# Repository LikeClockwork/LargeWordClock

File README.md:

# Like Clockwork Large Word Clock Design Files and Software

This repository holds the PCB/laser etch design files and Arduino code for my version of the word clock.

These PCBs and the laser cut glass faces are currently available via my store at: http://www.likeclockworkdesign.com/collections/kits/products/the-standard-makers-kit

The PCB measures 399x399mm and the glass faceplace measures 17"x17".

The PCBs are Arduino compatible and it runs the “Arduino on a breadboard” bootloader. The microcontroller is a Atmega328p (TQFP package) running at 8MHz that drives two 16x8 LED (256 LEDs) matrixes via two HT16K33’s. Time keeping is accomplished using a DS321 real time clock.  There is a linear power regulator on board to step down 9-12V input voltage to 5V. 

All unused Arduino pins are broken out to a pin header. Happy hacking!

The posted PCBs have been fabricated, assembled, and confirmed as working with the posted code.

*Upcoming Changes:*

The boards shipped ~~for the Kickstarter~~ going forward will have the following enhancements:
+ Addition of a footprint so that you can plug in standard Arduino shields. Done!

+ The ability to replace all ICs with prebuilt modules (Arduino Nano vs. Atmega328p, Adafruit matrix drivers vs. HT16K33s) for those who don’t want to drag solder tiny leads. Done!

+ Addition of a prototyping area to make use of all that extra real-estate. Done!

+ Addition of an Open Source Hardware logo. Done!

*Thanks to:*

+ The Kickstarter Backers
+ CERN for building KiCad and making it free.
+ Adafruit for their great libraries and making awesome breakout boards.

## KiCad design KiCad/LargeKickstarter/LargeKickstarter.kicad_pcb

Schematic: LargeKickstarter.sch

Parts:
0-0, 0-1, 0-2, 0-3, 0-4, 0-5, 0-6, 0-7, 0-8, 0-9, 0-10, 0-11, 0-12, 0-13, 0-14, 0-15, 0-16, 0-17, 0-18, 0-19, 0-20, 0-21, 0-22, 0-23, 0-24, 0-25, 0-26, 0-27, 0-28, 0-29, 0-30, 0-31, 1-0, 1-1, 1-2, 1-3, 1-4, 1-5, 1-6, 1-7, 1-8, 1-9, 1-10, 1-11, 1-12, 1-13, 1-14, 1-15, 1-16, 1-17, 1-18, 1-19, 1-20, 1-21, 1-22, 1-23, 1-24, 1-25, 1-26, 1-27, 1-28, 1-29, 1-30, 1-31, 2-0, 2-1, 2-2, 2-3, 2-4, 2-5, 2-6, 2-7, 2-8, 2-9, 2-10, 2-11, 2-12, 2-13, 2-14, 2-15, 2-16, 2-17, 2-18, 2-19, 2-20, 2-21, 2-22, 2-23, 2-24, 2-25, 2-26, 2-27, 2-28, 2-29, 2-30, 2-31, 3-0, 3-1, 3-2, 3-3, 3-4, 3-5, 3-6, 3-7, 3-8, 3-9, 3-10, 3-11, 3-12, 3-13, 3-14, 3-15, 3-16, 3-17, 3-18, 3-19, 3-20, 3-21, 3-22, 3-23, 3-24, 3-25, 3-26, 3-27, 3-28, 3-29, 3-30, 3-31, 4-0, 4-1, 4-2, 4-3, 4-4, 4-5, 4-6, 4-7, 4-8, 4-9, 4-10, 4-11, 4-12, 4-13, 4-14, 4-15, 4-16, 4-17, 4-18, 4-19, 4-20, 4-21, 4-22, 4-23, 4-24, 4-25, 4-26, 4-27, 4-28, 4-29, 4-30, 4-31, 5-0, 5-1, 5-2, 5-3, 5-4, 5-5, 5-6, 5-7, 5-8, 5-9, 5-10, 5-11, 5-12, 5-13, 5-14, 5-15, 5-16, 5-17, 5-18, 5-19, 5-20, 5-21, 5-22, 5-23, 5-24, 5-25, 5-26, 5-27, 5-28, 5-29, 5-30, 5-31, 6-0, 6-1, 6-2, 6-3, 6-4, 6-5, 6-6, 6-7, 6-8, 6-9, 6-10, 6-11, 6-12, 6-13, 6-14, 6-15, 6-16, 6-17, 6-18, 6-19, 6-20, 6-21, 6-22, 6-23, 6-24, 6-25, 6-26, 6-27, 6-28, 6-29, 6-30, 6-31, 7-0, 7-1, 7-2, 7-3, 7-4, 7-5, 7-6, 7-7, 7-8, 7-9, 7-10, 7-11, 7-12, 7-13, 7-14, 7-15, 7-16, 7-17, 7-18, 7-19, 7-20, 7-21, 7-22, 7-23, 7-24, 7-25, 7-26, 7-27, 7-28, 7-29, 7-30, 7-31, 8-0, 8-1, 8-2, 8-3, 8-4, 8-5, 8-6, 8-7, 8-8, 8-9, 8-10, 8-11, 8-12, 8-13, 8-14, 8-15, 8-16, 8-17, 8-18, 8-19, 8-20, 8-21, 8-22, 8-23, 8-24, 8-25, 8-26, 8-27, 8-28, 8-29, 8-30, 8-31, 9-0, 9-1, 9-2, 9-3, 9-4, 9-5, 9-6, 9-7, 9-8, 9-9, 9-10, 9-11, 9-12, 9-13, 9-14, 9-15, 9-16, 9-17, 9-18, 9-19, 9-20, 9-21, 9-22, 9-23, 9-24, 9-25, 9-26, 9-27, 9-28, 9-29, 9-30, 9-31, 10-0, 10-1, 10-2, 10-3, 10-4, 10-5, 10-6, 10-7, 10-8, 10-9, 10-10, 10-11, 10-12, 10-13, 10-14, 10-15, 10-16, 10-17, 10-18, 10-19, 10-20, 10-21, 10-22, 10-23, 10-24, 10-25, 10-26, 10-27, 10-28, 10-29, 10-30, 10-31, 11-0, 11-1, 11-2, 11-3, 11-4, 11-5, 11-6, 11-7, 11-8, 11-9, 11-10, 11-11, 11-12, 11-13, 11-14, 11-15, 11-16, 11-17, 11-18, 11-19, 11-20, 11-21, 11-22, 11-23, 11-24, 11-25, 11-26, 11-27, 11-28, 11-29, 11-30, 11-31, 12-0, 12-1, 12-2, 12-3, 12-4, 12-5, 12-6, 12-7, 12-8, 12-9, 12-10, 12-11, 12-12, 12-13, 12-14, 12-15, 12-16, 12-17, 12-18, 12-19, 12-20, 12-21, 12-22, 12-23, 12-24, 12-25, 12-26, 12-27, 12-28, 12-29, 12-30, 12-31, 13-0, 13-1, 13-2, 13-3, 13-4, 13-5, 13-6, 13-7, 13-8, 13-9, 13-10, 13-11, 13-12, 13-13, 13-14, 13-15, 13-16, 13-17, 13-18, 13-19, 13-20, 13-21, 13-22, 13-23, 13-24, 13-25, 13-26, 13-27, 13-28, 13-29, 13-30, 13-31, 14-0, 14-1, 14-2, 14-3, 14-4, 14-5, 14-6, 14-7, 14-8, 14-9, 14-10, 14-11, 14-12, 14-13, 14-14, 14-15, 14-16, 14-17, 14-18, 14-19, 14-20, 14-21, 14-22, 14-23, 14-24, 14-25, 14-26, 14-27, 14-28, 14-29, 14-30, 14-31, 15-0, 15-1, 15-2, 15-3, 15-4, 15-5, 15-6, 15-7, 15-8, 15-9, 15-10, 15-11, 15-12, 15-13, 15-14, 15-15, 15-16, 15-17, 15-18, 15-19, 15-20, 15-21, 15-22, 15-23, 15-24, 15-25, 15-26, 15-27, 15-28, 15-29, 15-30, 15-31: LED; SMD_LED_PLCC_2
BT1: BATTERY; BATTCOM_20MM_PTH
C1, C4, C5, C6, C7, C8: 0.1uF; C_0603_HandSoldering
C2: 10uF; Elko_vert_11.2x7.5mm_RM2.5_CopperClear
C3: 1uF; Elko_vert_11.2x7.5mm_RM2.5_CopperClear
D1: DIODE; Diode-SMA_Handsoldering
D2, D3, D4, D5: DIODE; SOD-323
JP1, JP2, JP3, JP4, JP5, JP6, JP7, JP8, JP9, JP10, JP11, JP12: JUMPER; solder_jumper
P1: CONN_01X03; Diode_TO-220_Dual_CommonCathode_Horizontal_LargePads
P2: CONN_01X02; Pin_Header_Straight_1x02
P4: CONN_02X03; Pin_Header_Straight_2x03
R1, R2, R4, R5, R7: 10K; R_0603_HandSoldering
R3, R6, R8, R9, R10, R11, R12, R13, R14, R15, R16, R17: 47K; R_0603_HandSoldering
SW1: HOUR; TACTILE-PTH-SIDEEZ
SW2: MIN; TACTILE-PTH-SIDEEZ
SW4: SOFT; TACTILE-PTH-SIDEEZ
U1, U4, U10, U12: HT16K33; SO28W
U2: DS3231; SOIC-16_7.5x10.3mm_Pitch1.27mm
U3: ATMEGA328-TQFP; TQFP32-08
U5, U6, U9, U11: HT16K33_BOUT; HT16K33_Breakout
U7: Arduino_Nano
U8: UNO_FOOTPRINT; shield_footprint

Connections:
2: U3.32 (2), U7.5 (2), U8.30 (2)
3: U3.1 (3), U7.6 (3), U8.29 (3)
3.3V: U7.29 (3.3V), U8.4 (3.3V)
4: U3.2 (4), U7.7 (4), U8.28 (4)
5: R1.1, SW1.2, U3.9 (5), U7.8 (5), U8.27 (5); also elsewhere on the board
6: R2.1, SW2.2, U3.10 (6), U7.9 (6), U8.26 (6); also elsewhere on the board
7: R5.1, SW4.2, U3.11 (7), U7.10 (7), U8.25 (7); also elsewhere on the board
8: U3.12 (8), U7.11 (8), U8.24 (8)
9: U3.13 (9), U7.12 (9), U8.23 (9)
10: U3.14 (10), U7.13 (10/SS), U8.22 (10)
A0: U3.23 (A0), U7.27 (A0), U8.9 (A0)
A1: U3.24 (A1), U7.26 (A1), U8.10 (A1)
A2: U3.25 (A2), U7.25 (A2), U8.11 (A2)
A3: U3.26 (A3), U7.24 (A3), U8.12 (A3)
A6: U3.19 (A6), U7.21 (A6)
A7: U3.22 (A7), U7.20 (A7)
AREF: U3.20 (AREF), U7.28 (AREF), U8.17 (AREF)
COM-0-0: 0-0.2 (K), 1-0.2 (K), 2-0.2 (K), 3-0.2 (K), 4-0.2 (K), 5-0.2 (K), 6-0.2 (K), 7-0.2 (K), 8-0.2 (K), 9-0.2 (K), 10-0.2 (K), 11-0.2 (K), 12-0.2 (K), 13-0.2 (K), 14-0.2 (K), 15-0.2 (K), D3.2 (A), U1.2 (COM0/AD), U5.2 (COM0/A0)
COM-0-1: 0-1.2 (K), 1-1.2 (K), 2-1.2 (K), 3-1.2 (K), 4-1.2 (K), 5-1.2 (K), 6-1.2 (K), 7-1.2 (K), 8-1.2 (K), 9-1.2 (K), 10-1.2 (K), 11-1.2 (K), 12-1.2 (K), 13-1.2 (K), 14-1.2 (K), 15-1.2 (K), U1.3 (COM1), U5.3 (COM1)
COM-0-2: 0-2.2 (K), 1-2.2 (K), 2-2.2 (K), 3-2.2 (K), 4-2.2 (K), 5-2.2 (K), 6-2.2 (K), 7-2.2 (K), 8-2.2 (K), 9-2.2 (K), 10-2.2 (K), 11-2.2 (K), 12-2.2 (K), 13-2.2 (K), 14-2.2 (K), 15-2.2 (K), U1.4 (COM2), U5.4 (COM2)
COM-0-3: 0-3.2 (K), 1-3.2 (K), 2-3.2 (K), 3-3.2 (K), 4-3.2 (K), 5-3.2 (K), 6-3.2 (K), 7-3.2 (K), 8-3.2 (K), 9-3.2 (K), 10-3.2 (K), 11-3.2 (K), 12-3.2 (K), 13-3.2 (K), 14-3.2 (K), 15-3.2 (K), U1.5 (COM3), U5.5 (COM3)
COM-0-4: 0-4.2 (K), 1-4.2 (K), 2-4.2 (K), 3-4.2 (K), 4-4.2 (K), 5-4.2 (K), 6-4.2 (K), 7-4.2 (K), 8-4.2 (K), 9-4.2 (K), 10-4.2 (K), 11-4.2 (K), 12-4.2 (K), 13-4.2 (K), 14-4.2 (K), 15-4.2 (K), U1.6 (COM4), U5.6 (COM4)
COM-0-5: 0-5.2 (K), 1-5.2 (K), 2-5.2 (K), 3-5.2 (K), 4-5.2 (K), 5-5.2 (K), 6-5.2 (K), 7-5.2 (K), 8-5.2 (K), 9-5.2 (K), 10-5.2 (K), 11-5.2 (K), 12-5.2 (K), 13-5.2 (K), 14-5.2 (K), 15-5.2 (K), U1.7 (COM5), U5.7 (COM5)
COM-0-6: 0-6.2 (K), 1-6.2 (K), 2-6.2 (K), 3-6.2 (K), 4-6.2 (K), 5-6.2 (K), 6-6.2 (K), 7-6.2 (K), 8-6.2 (K), 9-6.2 (K), 10-6.2 (K), 11-6.2 (K), 12-6.2 (K), 13-6.2 (K), 14-6.2 (K), 15-6.2 (K), U1.8 (COM6), U5.8 (COM6)
COM-0-7: 0-7.2 (K), 1-7.2 (K), 2-7.2 (K), 3-7.2 (K), 4-7.2 (K), 5-7.2 (K), 6-7.2 (K), 7-7.2 (K), 8-7.2 (K), 9-7.2 (K), 10-7.2 (K), 11-7.2 (K), 12-7.2 (K), 13-7.2 (K), 14-7.2 (K), 15-7.2 (K), U1.9 (COM7), U5.9 (COM7)
COM-1-0: 0-8.2 (K), 1-8.2 (K), 2-8.2 (K), 3-8.2 (K), 4-8.2 (K), 5-8.2 (K), 6-8.2 (K), 7-8.2 (K), 8-8.2 (K), 9-8.2 (K), 10-8.2 (K), 11-8.2 (K), 12-8.2 (K), 13-8.2 (K), 14-8.2 (K), 15-8.2 (K), D2.2 (A), U4.2 (COM0/AD), U6.2 (COM0/A0)
COM-1-1: 0-9.2 (K), 1-9.2 (K), 2-9.2 (K), 3-9.2 (K), 4-9.2 (K), 5-9.2 (K), 6-9.2 (K), 7-9.2 (K), 8-9.2 (K), 9-9.2 (K), 10-9.2 (K), 11-9.2 (K), 12-9.2 (K), 13-9.2 (K), 14-9.2 (K), 15-9.2 (K), U4.3 (COM1), U6.3 (COM1)
COM-1-2: 0-10.2 (K), 1-10.2 (K), 2-10.2 (K), 3-10.2 (K), 4-10.2 (K), 5-10.2 (K), 6-10.2 (K), 7-10.2 (K), 8-10.2 (K), 9-10.2 (K), 10-10.2 (K), 11-10.2 (K), 12-10.2 (K), 13-10.2 (K), 14-10.2 (K), 15-10.2 (K), U4.4 (COM2), U6.4 (COM2)
COM-1-3: 0-11.2 (K), 1-11.2 (K), 2-11.2 (K), 3-11.2 (K), 4-11.2 (K), 5-11.2 (K), 6-11.2 (K), 7-11.2 (K), 8-11.2 (K), 9-11.2 (K), 10-11.2 (K), 11-11.2 (K), 12-11.2 (K), 13-11.2 (K), 14-11.2 (K), 15-11.2 (K), U4.5 (COM3), U6.5 (COM3)
COM-1-4: 0-12.2 (K), 1-12.2 (K), 2-12.2 (K), 3-12.2 (K), 4-12.2 (K), 5-12.2 (K), 6-12.2 (K), 7-12.2 (K), 8-12.2 (K), 9-12.2 (K), 10-12.2 (K), 11-12.2 (K), 12-12.2 (K), 13-12.2 (K), 14-12.2 (K), 15-12.2 (K), U4.6 (COM4), U6.6 (COM4)
COM-1-5: 0-13.2 (K), 1-13.2 (K), 2-13.2 (K), 3-13.2 (K), 4-13.2 (K), 5-13.2 (K), 6-13.2 (K), 7-13.2 (K), 8-13.2 (K), 9-13.2 (K), 10-13.2 (K), 11-13.2 (K), 12-13.2 (K), 13-13.2 (K), 14-13.2 (K), 15-13.2 (K), U4.7 (COM5), U6.7 (COM5)
COM-1-6: 0-14.2 (K), 1-14.2 (K), 2-14.2 (K), 3-14.2 (K), 4-14.2 (K), 5-14.2 (K), 6-14.2 (K), 7-14.2 (K), 8-14.2 (K), 9-14.2 (K), 10-14.2 (K), 11-14.2 (K), 12-14.2 (K), 13-14.2 (K), 14-14.2 (K), 15-14.2 (K), U4.8 (COM6), U6.8 (COM6)
COM-1-7: 0-15.2 (K), 1-15.2 (K), 2-15.2 (K), 3-15.2 (K), 4-15.2 (K), 5-15.2 (K), 6-15.2 (K), 7-15.2 (K), 8-15.2 (K), 9-15.2 (K), 10-15.2 (K), 11-15.2 (K), 12-15.2 (K), 13-15.2 (K), 14-15.2 (K), 15-15.2 (K), U4.9 (COM7), U6.9 (COM7)
COM-2-0: 0-16.2 (K), 1-16.2 (K), 2-16.2 (K), 3-16.2 (K), 4-16.2 (K), 5-16.2 (K), 6-16.2 (K), 7-16.2 (K), 8-16.2 (K), 9-16.2 (K), 10-16.2 (K), 11-16.2 (K), 12-16.2 (K), 13-16.2 (K), 14-16.2 (K), 15-16.2 (K), D4.2 (A), U9.2 (COM0/A0), U10.2 (COM0/AD)
COM-2-1: 0-17.2 (K), 1-17.2 (K), 2-17.2 (K), 3-17.2 (K), 4-17.2 (K), 5-17.2 (K), 6-17.2 (K), 7-17.2 (K), 8-17.2 (K), 9-17.2 (K), 10-17.2 (K), 11-17.2 (K), 12-17.2 (K), 13-17.2 (K), 14-17.2 (K), 15-17.2 (K), U9.3 (COM1), U10.3 (COM1)
COM-2-2: 0-18.2 (K), 1-18.2 (K), 2-18.2 (K), 3-18.2 (K), 4-18.2 (K), 5-18.2 (K), 6-18.2 (K), 7-18.2 (K), 8-18.2 (K), 9-18.2 (K), 10-18.2 (K), 11-18.2 (K), 12-18.2 (K), 13-18.2 (K), 14-18.2 (K), 15-18.2 (K), U9.4 (COM2), U10.4 (COM2)
COM-2-3: 0-19.2 (K), 1-19.2 (K), 2-19.2 (K), 3-19.2 (K), 4-19.2 (K), 5-19.2 (K), 6-19.2 (K), 7-19.2 (K), 8-19.2 (K), 9-19.2 (K), 10-19.2 (K), 11-19.2 (K), 12-19.2 (K), 13-19.2 (K), 14-19.2 (K), 15-19.2 (K), U9.5 (COM3), U10.5 (COM3)
COM-2-4: 0-20.2 (K), 1-20.2 (K), 2-20.2 (K), 3-20.2 (K), 4-20.2 (K), 5-20.2 (K), 6-20.2 (K), 7-20.2 (K), 8-20.2 (K), 9-20.2 (K), 10-20.2 (K), 11-20.2 (K), 12-20.2 (K), 13-20.2 (K), 14-20.2 (K), 15-20.2 (K), U9.6 (COM4), U10.6 (COM4)
COM-2-5: 0-21.2 (K), 1-21.2 (K), 2-21.2 (K), 3-21.2 (K), 4-21.2 (K), 5-21.2 (K), 6-21.2 (K), 7-21.2 (K), 8-21.2 (K), 9-21.2 (K), 10-21.2 (K), 11-21.2 (K), 12-21.2 (K), 13-21.2 (K), 14-21.2 (K), 15-21.2 (K), U9.7 (COM5), U10.7 (COM5)
COM-2-6: 0-22.2 (K), 1-22.2 (K), 2-22.2 (K), 3-22.2 (K), 4-22.2 (K), 5-22.2 (K), 6-22.2 (K), 7-22.2 (K), 8-22.2 (K), 9-22.2 (K), 10-22.2 (K), 11-22.2 (K), 12-22.2 (K), 13-22.2 (K), 14-22.2 (K), 15-22.2 (K), U9.8 (COM6), U10.8 (COM6)
COM-2-7: 0-23.2 (K), 1-23.2 (K), 2-23.2 (K), 3-23.2 (K), 4-23.2 (K), 5-23.2 (K), 6-23.2 (K), 7-23.2 (K), 8-23.2 (K), 9-23.2 (K), 10-23.2 (K), 11-23.2 (K), 12-23.2 (K), 13-23.2 (K), 14-23.2 (K), 15-23.2 (K), U9.9 (COM7), U10.9 (COM7)
COM-3-0: 0-24.2 (K), 1-24.2 (K), 2-24.2 (K), 3-24.2 (K), 4-24.2 (K), 5-24.2 (K), 6-24.2 (K), 7-24.2 (K), 8-24.2 (K), 9-24.2 (K), 10-24.2 (K), 11-24.2 (K), 12-24.2 (K), 13-24.2 (K), 14-24.2 (K), 15-24.2 (K), D5.2 (A), U11.2 (COM0/A0), U12.2 (COM0/AD)
COM-3-1: 0-25.2 (K), 1-25.2 (K), 2-25.2 (K), 3-25.2 (K), 4-25.2 (K), 5-25.2 (K), 6-25.2 (K), 7-25.2 (K), 8-25.2 (K), 9-25.2 (K), 10-25.2 (K), 11-25.2 (K), 12-25.2 (K), 13-25.2 (K), 14-25.2 (K), 15-25.2 (K), U11.3 (COM1), U12.3 (COM1)
COM-3-2: 0-26.2 (K), 1-26.2 (K), 2-26.2 (K), 3-26.2 (K), 4-26.2 (K), 5-26.2 (K), 6-26.2 (K), 7-26.2 (K), 8-26.2 (K), 9-26.2 (K), 10-26.2 (K), 11-26.2 (K), 12-26.2 (K), 13-26.2 (K), 14-26.2 (K), 15-26.2 (K), U11.4 (COM2), U12.4 (COM2)
COM-3-3: 0-27.2 (K), 1-27.2 (K), 2-27.2 (K), 3-27.2 (K), 4-27.2 (K), 5-27.2 (K), 6-27.2 (K), 7-27.2 (K), 8-27.2 (K), 9-27.2 (K), 10-27.2 (K), 11-27.2 (K), 12-27.2 (K), 13-27.2 (K), 14-27.2 (K), 15-27.2 (K), U11.5 (COM3), U12.5 (COM3)
COM-3-4: 0-28.2 (K), 1-28.2 (K), 2-28.2 (K), 3-28.2 (K), 4-28.2 (K), 5-28.2 (K), 6-28.2 (K), 7-28.2 (K), 8-28.2 (K), 9-28.2 (K), 10-28.2 (K), 11-28.2 (K), 12-28.2 (K), 13-28.2 (K), 14-28.2 (K), 15-28.2 (K), U11.6 (COM4), U12.6 (COM4)
COM-3-5: 0-29.2 (K), 1-29.2 (K), 2-29.2 (K), 3-29.2 (K), 4-29.2 (K), 5-29.2 (K), 6-29.2 (K), 7-29.2 (K), 8-29.2 (K), 9-29.2 (K), 10-29.2 (K), 11-29.2 (K), 12-29.2 (K), 13-29.2 (K), 14-29.2 (K), 15-29.2 (K), U11.7 (COM5), U12.7 (COM5)
COM-3-6: 0-30.2 (K), 1-30.2 (K), 2-30.2 (K), 3-30.2 (K), 4-30.2 (K), 5-30.2 (K), 6-30.2 (K), 7-30.2 (K), 8-30.2 (K), 9-30.2 (K), 10-30.2 (K), 11-30.2 (K), 12-30.2 (K), 13-30.2 (K), 14-30.2 (K), 15-30.2 (K), U11.8 (COM6), U12.8 (COM6)
COM-3-7: 0-31.2 (K), 1-31.2 (K), 2-31.2 (K), 3-31.2 (K), 4-31.2 (K), 5-31.2 (K), 6-31.2 (K), 7-31.2 (K), 8-31.2 (K), 9-31.2 (K), 10-31.2 (K), 11-31.2 (K), 12-31.2 (K), 13-31.2 (K), 14-31.2 (K), 15-31.2 (K), U11.9 (COM7), U12.9 (COM7)
GND: BT1.2 (-), C1.2, C2.2, C3.2, C4.2, C5.2, C6.2, C7.2, C8.2, P1.2, P2.1, P4.6, R1.2, R2.2, R5.2, U1.1 (GND), U2.5 (N/C), U2.6 (N/C), U2.7 (N/C), U2.8 (N/C), U2.9 (N/C), U2.10 (N/C), U2.11 (N/C), U2.12 (N/C), U2.13 (GND), U3.3 (GND), U3.5 (GND), U3.21 (GND), U4.1 (GND), U5.1 (GND), U6.1 (GND), U7.4 (GND), U7.17 (GND), U8.6 (GND), U8.7 (GND), U8.18 (GND), U8.38 (GND), U9.1 (GND), U10.1 (GND), U11.1 (GND), U12.1 (GND); also elsewhere on the board
MISO: P4.1, U3.16 (12/MISO), U7.15 (12/MISO), U8.20 (12), U8.35 (MISO)
MOSI: P4.4, U3.15 (11/MOSI), U7.14 (11/MOSI), U8.21 (11), U8.37 (MOSI)
unnamed: BT1.1 (+), U2.14 (Vbat)
unnamed: D2.1 (K), R9.2, R10.2, R11.2
unnamed: D3.1 (K), R3.2, R6.2, R8.2
unnamed: D4.1 (K), R12.2, R13.2, R14.2
unnamed: D5.1 (K), R15.2, R16.2, R17.2
unnamed: JP1.1, R3.1
unnamed: JP2.1, R6.1
unnamed: JP3.1, R8.1
unnamed: JP4.1, R11.1
unnamed: JP5.1, R9.1
unnamed: JP6.1, R10.1
unnamed: JP7.1, R12.1
unnamed: JP8.1, R13.1
unnamed: JP9.1, R14.1
unnamed: JP10.1, R15.1
unnamed: JP11.1, R16.1
unnamed: JP12.1, R17.1
RAW: D1.2 (A), P2.2; also elsewhere on the board
ROW-0-0: 0-0.1 (A), 0-1.1 (A), 0-2.1 (A), 0-3.1 (A), 0-4.1 (A), 0-5.1 (A), 0-6.1 (A), 0-7.1 (A), JP1.2, U1.25 (ROW0/A2), U5.25 (ROW0/A2)
ROW-0-1: 1-0.1 (A), 1-1.1 (A), 1-2.1 (A), 1-3.1 (A), 1-4.1 (A), 1-5.1 (A), 1-6.1 (A), 1-7.1 (A), JP2.2, U1.24 (ROW1/A1), U5.24 (ROW1/A1)
ROW-0-2: 2-0.1 (A), 2-1.1 (A), 2-2.1 (A), 2-3.1 (A), 2-4.1 (A), 2-5.1 (A), 2-6.1 (A), 2-7.1 (A), JP3.2, U1.23 (ROW2/A0), U5.23 (ROW2/A0)
ROW-0-3: 3-0.1 (A), 3-1.1 (A), 3-2.1 (A), 3-3.1 (A), 3-4.1 (A), 3-5.1 (A), 3-6.1 (A), 3-7.1 (A), U1.22 (ROW3), U5.22 (ROW3)
ROW-0-4: 4-0.1 (A), 4-1.1 (A), 4-2.1 (A), 4-3.1 (A), 4-4.1 (A), 4-5.1 (A), 4-6.1 (A), 4-7.1 (A), U1.21 (ROW4), U5.21 (ROW4)
ROW-0-5: 5-0.1 (A), 5-1.1 (A), 5-2.1 (A), 5-3.1 (A), 5-4.1 (A), 5-5.1 (A), 5-6.1 (A), 5-7.1 (A), U1.20 (ROW5), U5.20 (ROW5)
ROW-0-6: 6-0.1 (A), 6-1.1 (A), 6-2.1 (A), 6-3.1 (A), 6-4.1 (A), 6-5.1 (A), 6-6.1 (A), 6-7.1 (A), U1.19 (ROW6), U5.19 (ROW6)
ROW-0-7: 7-0.1 (A), 7-1.1 (A), 7-2.1 (A), 7-3.1 (A), 7-4.1 (A), 7-5.1 (A), 7-6.1 (A), 7-7.1 (A), U1.18 (ROW7), U5.18 (ROW7)
ROW-0-8: 8-0.1 (A), 8-1.1 (A), 8-2.1 (A), 8-3.1 (A), 8-4.1 (A), 8-5.1 (A), 8-6.1 (A), 8-7.1 (A), U1.17 (ROW8), U5.17 (ROW8)
ROW-0-9: 9-0.1 (A), 9-1.1 (A), 9-2.1 (A), 9-3.1 (A), 9-4.1 (A), 9-5.1 (A), 9-6.1 (A), 9-7.1 (A), U1.16 (ROW9), U5.16 (ROW9)
ROW-0-10: 10-0.1 (A), 10-1.1 (A), 10-2.1 (A), 10-3.1 (A), 10-4.1 (A), 10-5.1 (A), 10-6.1 (A), 10-7.1 (A), U1.15 (ROW10), U5.15 (ROW10)
ROW-0-11: 11-0.1 (A), 11-1.1 (A), 11-2.1 (A), 11-3.1 (A), 11-4.1 (A), 11-5.1 (A), 11-6.1 (A), 11-7.1 (A), U1.14 (ROW11), U5.14 (ROW11)
ROW-0-12: 12-0.1 (A), 12-1.1 (A), 12-2.1 (A), 12-3.1 (A), 12-4.1 (A), 12-5.1 (A), 12-6.1 (A), 12-7.1 (A), U1.13 (ROW12), U5.13 (ROW12)
ROW-0-13: 13-0.1 (A), 13-1.1 (A), 13-2.1 (A), 13-3.1 (A), 13-4.1 (A), 13-5.1 (A), 13-6.1 (A), 13-7.1 (A), U1.12 (ROW13), U5.12 (ROW13)
ROW-0-14: 14-0.1 (A), 14-1.1 (A), 14-2.1 (A), 14-3.1 (A), 14-4.1 (A), 14-5.1 (A), 14-6.1 (A), 14-7.1 (A), U1.11 (ROW14), U5.11 (ROW14)
ROW-0-15: 15-0.1 (A), 15-1.1 (A), 15-2.1 (A), 15-3.1 (A), 15-4.1 (A), 15-5.1 (A), 15-6.1 (A), 15-7.1 (A), U1.10 (ROW15), U5.10 (ROW15)
ROW-1-0: 0-8.1 (A), 0-9.1 (A), 0-10.1 (A), 0-11.1 (A), 0-12.1 (A), 0-13.1 (A), 0-14.1 (A), 0-15.1 (A), JP4.2, U4.25 (ROW0/A2), U6.25 (ROW0/A2)
ROW-1-1: 1-8.1 (A), 1-9.1 (A), 1-10.1 (A), 1-11.1 (A), 1-12.1 (A), 1-13.1 (A), 1-14.1 (A), 1-15.1 (A), JP5.2, U4.24 (ROW1/A1), U6.24 (ROW1/A1)
ROW-1-2: 2-8.1 (A), 2-9.1 (A), 2-10.1 (A), 2-11.1 (A), 2-12.1 (A), 2-13.1 (A), 2-14.1 (A), 2-15.1 (A), JP6.2, U4.23 (ROW2/A0), U6.23 (ROW2/A0)
ROW-1-3: 3-8.1 (A), 3-9.1 (A), 3-10.1 (A), 3-11.1 (A), 3-12.1 (A), 3-13.1 (A), 3-14.1 (A), 3-15.1 (A), U4.22 (ROW3), U6.22 (ROW3)
ROW-1-4: 4-8.1 (A), 4-9.1 (A), 4-10.1 (A), 4-11.1 (A), 4-12.1 (A), 4-13.1 (A), 4-14.1 (A), 4-15.1 (A), U4.21 (ROW4), U6.21 (ROW4)
ROW-1-5: 5-8.1 (A), 5-9.1 (A), 5-10.1 (A), 5-11.1 (A), 5-12.1 (A), 5-13.1 (A), 5-14.1 (A), 5-15.1 (A), U4.20 (ROW5), U6.20 (ROW5)
ROW-1-6: 6-8.1 (A), 6-9.1 (A), 6-10.1 (A), 6-11.1 (A), 6-12.1 (A), 6-13.1 (A), 6-14.1 (A), 6-15.1 (A), U4.19 (ROW6), U6.19 (ROW6)
ROW-1-7: 7-8.1 (A), 7-9.1 (A), 7-10.1 (A), 7-11.1 (A), 7-12.1 (A), 7-13.1 (A), 7-14.1 (A), 7-15.1 (A), U4.18 (ROW7), U6.18 (ROW7)
ROW-1-8: 8-8.1 (A), 8-9.1 (A), 8-10.1 (A), 8-11.1 (A), 8-12.1 (A), 8-13.1 (A), 8-14.1 (A), 8-15.1 (A), U4.17 (ROW8), U6.17 (ROW8)
ROW-1-9: 9-8.1 (A), 9-9.1 (A), 9-10.1 (A), 9-11.1 (A), 9-12.1 (A), 9-13.1 (A), 9-14.1 (A), 9-15.1 (A), U4.16 (ROW9), U6.16 (ROW9)
ROW-1-10: 10-8.1 (A), 10-9.1 (A), 10-10.1 (A), 10-11.1 (A), 10-12.1 (A), 10-13.1 (A), 10-14.1 (A), 10-15.1 (A), U4.15 (ROW10), U6.15 (ROW10)
ROW-1-11: 11-8.1 (A), 11-9.1 (A), 11-10.1 (A), 11-11.1 (A), 11-12.1 (A), 11-13.1 (A), 11-14.1 (A), 11-15.1 (A), U4.14 (ROW11), U6.14 (ROW11)
ROW-1-12: 12-8.1 (A), 12-9.1 (A), 12-10.1 (A), 12-11.1 (A), 12-12.1 (A), 12-13.1 (A), 12-14.1 (A), 12-15.1 (A), U4.13 (ROW12), U6.13 (ROW12)
ROW-1-13: 13-8.1 (A), 13-9.1 (A), 13-10.1 (A), 13-11.1 (A), 13-12.1 (A), 13-13.1 (A), 13-14.1 (A), 13-15.1 (A), U4.12 (ROW13), U6.12 (ROW13)
ROW-1-14: 14-8.1 (A), 14-9.1 (A), 14-10.1 (A), 14-11.1 (A), 14-12.1 (A), 14-13.1 (A), 14-14.1 (A), 14-15.1 (A), U4.11 (ROW14), U6.11 (ROW14)
ROW-1-15: 15-8.1 (A), 15-9.1 (A), 15-10.1 (A), 15-11.1 (A), 15-12.1 (A), 15-13.1 (A), 15-14.1 (A), 15-15.1 (A), U4.10 (ROW15), U6.10 (ROW15)
ROW-2-0: 0-16.1 (A), 0-17.1 (A), 0-18.1 (A), 0-19.1 (A), 0-20.1 (A), 0-21.1 (A), 0-22.1 (A), 0-23.1 (A), JP7.2, U9.25 (ROW0/A2), U10.25 (ROW0/A2)
ROW-2-1: 1-16.1 (A), 1-17.1 (A), 1-18.1 (A), 1-19.1 (A), 1-20.1 (A), 1-21.1 (A), 1-22.1 (A), 1-23.1 (A), JP8.2, U9.24 (ROW1/A1), U10.24 (ROW1/A1)
ROW-2-2: 2-16.1 (A), 2-17.1 (A), 2-18.1 (A), 2-19.1 (A), 2-20.1 (A), 2-21.1 (A), 2-22.1 (A), 2-23.1 (A), JP9.2, U9.23 (ROW2/A0), U10.23 (ROW2/A0)
ROW-2-3: 3-16.1 (A), 3-17.1 (A), 3-18.1 (A), 3-19.1 (A), 3-20.1 (A), 3-21.1 (A), 3-22.1 (A), 3-23.1 (A), U9.22 (ROW3), U10.22 (ROW3)
ROW-2-4: 4-16.1 (A), 4-17.1 (A), 4-18.1 (A), 4-19.1 (A), 4-20.1 (A), 4-21.1 (A), 4-22.1 (A), 4-23.1 (A), U9.21 (ROW4), U10.21 (ROW4)
ROW-2-5: 5-16.1 (A), 5-17.1 (A), 5-18.1 (A), 5-19.1 (A), 5-20.1 (A), 5-21.1 (A), 5-22.1 (A), 5-23.1 (A), U9.20 (ROW5), U10.20 (ROW5)
ROW-2-6: 6-16.1 (A), 6-17.1 (A), 6-18.1 (A), 6-19.1 (A), 6-20.1 (A), 6-21.1 (A), 6-22.1 (A), 6-23.1 (A), U9.19 (ROW6), U10.19 (ROW6)
ROW-2-7: 7-16.1 (A), 7-17.1 (A), 7-18.1 (A), 7-19.1 (A), 7-20.1 (A), 7-21.1 (A), 7-22.1 (A), 7-23.1 (A), U9.18 (ROW7), U10.18 (ROW7)
ROW-2-8: 8-16.1 (A), 8-17.1 (A), 8-18.1 (A), 8-19.1 (A), 8-20.1 (A), 8-21.1 (A), 8-22.1 (A), 8-23.1 (A), U9.17 (ROW8), U10.17 (ROW8)
ROW-2-9: 9-16.1 (A), 9-17.1 (A), 9-18.1 (A), 9-19.1 (A), 9-20.1 (A), 9-21.1 (A), 9-22.1 (A), 9-23.1 (A), U9.16 (ROW9), U10.16 (ROW9)
ROW-2-10: 10-16.1 (A), 10-17.1 (A), 10-18.1 (A), 10-19.1 (A), 10-20.1 (A), 10-21.1 (A), 10-22.1 (A), 10-23.1 (A), U9.15 (ROW10), U10.15 (ROW10)
ROW-2-11: 11-16.1 (A), 11-17.1 (A), 11-18.1 (A), 11-19.1 (A), 11-20.1 (A), 11-21.1 (A), 11-22.1 (A), 11-23.1 (A), U9.14 (ROW11), U10.14 (ROW11)
ROW-2-12: 12-16.1 (A), 12-17.1 (A), 12-18.1 (A), 12-19.1 (A), 12-20.1 (A), 12-21.1 (A), 12-22.1 (A), 12-23.1 (A), U9.13 (ROW12), U10.13 (ROW12)
ROW-2-13: 13-16.1 (A), 13-17.1 (A), 13-18.1 (A), 13-19.1 (A), 13-20.1 (A), 13-21.1 (A), 13-22.1 (A), 13-23.1 (A), U9.12 (ROW13), U10.12 (ROW13)
ROW-2-14: 14-16.1 (A), 14-17.1 (A), 14-18.1 (A), 14-19.1 (A), 14-20.1 (A), 14-21.1 (A), 14-22.1 (A), 14-23.1 (A), U9.11 (ROW14), U10.11 (ROW14)
ROW-2-15: 15-16.1 (A), 15-17.1 (A), 15-18.1 (A), 15-19.1 (A), 15-20.1 (A), 15-21.1 (A), 15-22.1 (A), 15-23.1 (A), U9.10 (ROW15), U10.10 (ROW15)
ROW-3-0: 0-24.1 (A), 0-25.1 (A), 0-26.1 (A), 0-27.1 (A), 0-28.1 (A), 0-29.1 (A), 0-30.1 (A), 0-31.1 (A), JP10.2, U11.25 (ROW0/A2), U12.25 (ROW0/A2)
ROW-3-1: 1-24.1 (A), 1-25.1 (A), 1-26.1 (A), 1-27.1 (A), 1-28.1 (A), 1-29.1 (A), 1-30.1 (A), 1-31.1 (A), JP11.2, U11.24 (ROW1/A1), U12.24 (ROW1/A1)
ROW-3-2: 2-24.1 (A), 2-25.1 (A), 2-26.1 (A), 2-27.1 (A), 2-28.1 (A), 2-29.1 (A), 2-30.1 (A), 2-31.1 (A), JP12.2, U11.23 (ROW2/A0), U12.23 (ROW2/A0)
ROW-3-3: 3-24.1 (A), 3-25.1 (A), 3-26.1 (A), 3-27.1 (A), 3-28.1 (A), 3-29.1 (A), 3-30.1 (A), 3-31.1 (A), U11.22 (ROW3), U12.22 (ROW3)
ROW-3-4: 4-24.1 (A), 4-25.1 (A), 4-26.1 (A), 4-27.1 (A), 4-28.1 (A), 4-29.1 (A), 4-30.1 (A), 4-31.1 (A), U11.21 (ROW4), U12.21 (ROW4)
ROW-3-5: 5-24.1 (A), 5-25.1 (A), 5-26.1 (A), 5-27.1 (A), 5-28.1 (A), 5-29.1 (A), 5-30.1 (A), 5-31.1 (A), U11.20 (ROW5), U12.20 (ROW5)
ROW-3-6: 6-24.1 (A), 6-25.1 (A), 6-26.1 (A), 6-27.1 (A), 6-28.1 (A), 6-29.1 (A), 6-30.1 (A), 6-31.1 (A), U11.19 (ROW6), U12.19 (ROW6)
ROW-3-7: 7-24.1 (A), 7-25.1 (A), 7-26.1 (A), 7-27.1 (A), 7-28.1 (A), 7-29.1 (A), 7-30.1 (A), 7-31.1 (A), U11.18 (ROW7), U12.18 (ROW7)
ROW-3-8: 8-24.1 (A), 8-25.1 (A), 8-26.1 (A), 8-27.1 (A), 8-28.1 (A), 8-29.1 (A), 8-30.1 (A), 8-31.1 (A), U11.17 (ROW8), U12.17 (ROW8)
ROW-3-9: 9-24.1 (A), 9-25.1 (A), 9-26.1 (A), 9-27.1 (A), 9-28.1 (A), 9-29.1 (A), 9-30.1 (A), 9-31.1 (A), U11.16 (ROW9), U12.16 (ROW9)
ROW-3-10: 10-24.1 (A), 10-25.1 (A), 10-26.1 (A), 10-27.1 (A), 10-28.1 (A), 10-29.1 (A), 10-30.1 (A), 10-31.1 (A), U11.15 (ROW10), U12.15 (ROW10)
ROW-3-11: 11-24.1 (A), 11-25.1 (A), 11-26.1 (A), 11-27.1 (A), 11-28.1 (A), 11-29.1 (A), 11-30.1 (A), 11-31.1 (A), U11.14 (ROW11), U12.14 (ROW11)
ROW-3-12: 12-24.1 (A), 12-25.1 (A), 12-26.1 (A), 12-27.1 (A), 12-28.1 (A), 12-29.1 (A), 12-30.1 (A), 12-31.1 (A), U11.13 (ROW12), U12.13 (ROW12)
ROW-3-13: 13-24.1 (A), 13-25.1 (A), 13-26.1 (A), 13-27.1 (A), 13-28.1 (A), 13-29.1 (A), 13-30.1 (A), 13-31.1 (A), U11.12 (ROW13), U12.12 (ROW13)
ROW-3-14: 14-24.1 (A), 14-25.1 (A), 14-26.1 (A), 14-27.1 (A), 14-28.1 (A), 14-29.1 (A), 14-30.1 (A), 14-31.1 (A), U11.11 (ROW14), U12.11 (ROW14)
ROW-3-15: 15-24.1 (A), 15-25.1 (A), 15-26.1 (A), 15-27.1 (A), 15-28.1 (A), 15-29.1 (A), 15-30.1 (A), 15-31.1 (A), U11.10 (ROW15), U12.10 (ROW15)
RST: P4.5, U3.29 (RST), U7.3 (RST), U7.18 (RST), U8.3 (RESET), U8.33 (RESET)
RX: U3.30 (0/RX), U7.2 (RX), U8.32 (RX)
SCK: P4.3, U3.17 (13/SCK), U7.30 (13/SCK), U8.19 (13), U8.34 (SCK)
SCL: R4.2, U1.26 (SCL), U2.16 (SCL), U3.28 (A5/SCL), U4.26 (SCL), U5.26 (SCL), U6.26 (SCL), U7.22 (A5/SCL), U8.14 (A5), U8.15 (SCL), U9.26 (SCL), U10.26 (SCL), U11.26 (SCL), U12.26 (SCL); also elsewhere on the board
SDA: R7.1, U1.27 (SDA), U2.15 (SDA), U3.27 (A4/SDA), U4.27 (SDA), U5.27 (SDA), U6.27 (SDA), U7.23 (A4/SDA), U8.13 (A4), U8.16 (SDA), U9.27 (SDA), U10.27 (SDA), U11.27 (SDA), U12.27 (SDA); also elsewhere on the board
TX: U3.31 (1/TX), U7.1 (TX), U8.31 (TX)
VCC: C1.1, C3.1, C4.1, C5.1, C6.1, C7.1, C8.1, P1.3, P4.2, R4.1, R7.2, SW1.1, SW2.1, SW4.1, U1.28 (Vcc), U2.2 (Vcc), U3.4 (VCC), U3.6 (VCC), U3.18 (AVCC), U4.28 (Vcc), U5.28 (VCC), U6.28 (VCC), U7.19 (5V), U8.5 (5V), U8.36 (5V), U9.28 (VCC), U10.28 (Vcc), U11.28 (VCC), U12.28 (Vcc); also elsewhere on the board
Vin: C2.1, D1.1 (K), P1.1, U7.16 (VIN), U8.8 (VIN); also elsewhere on the board

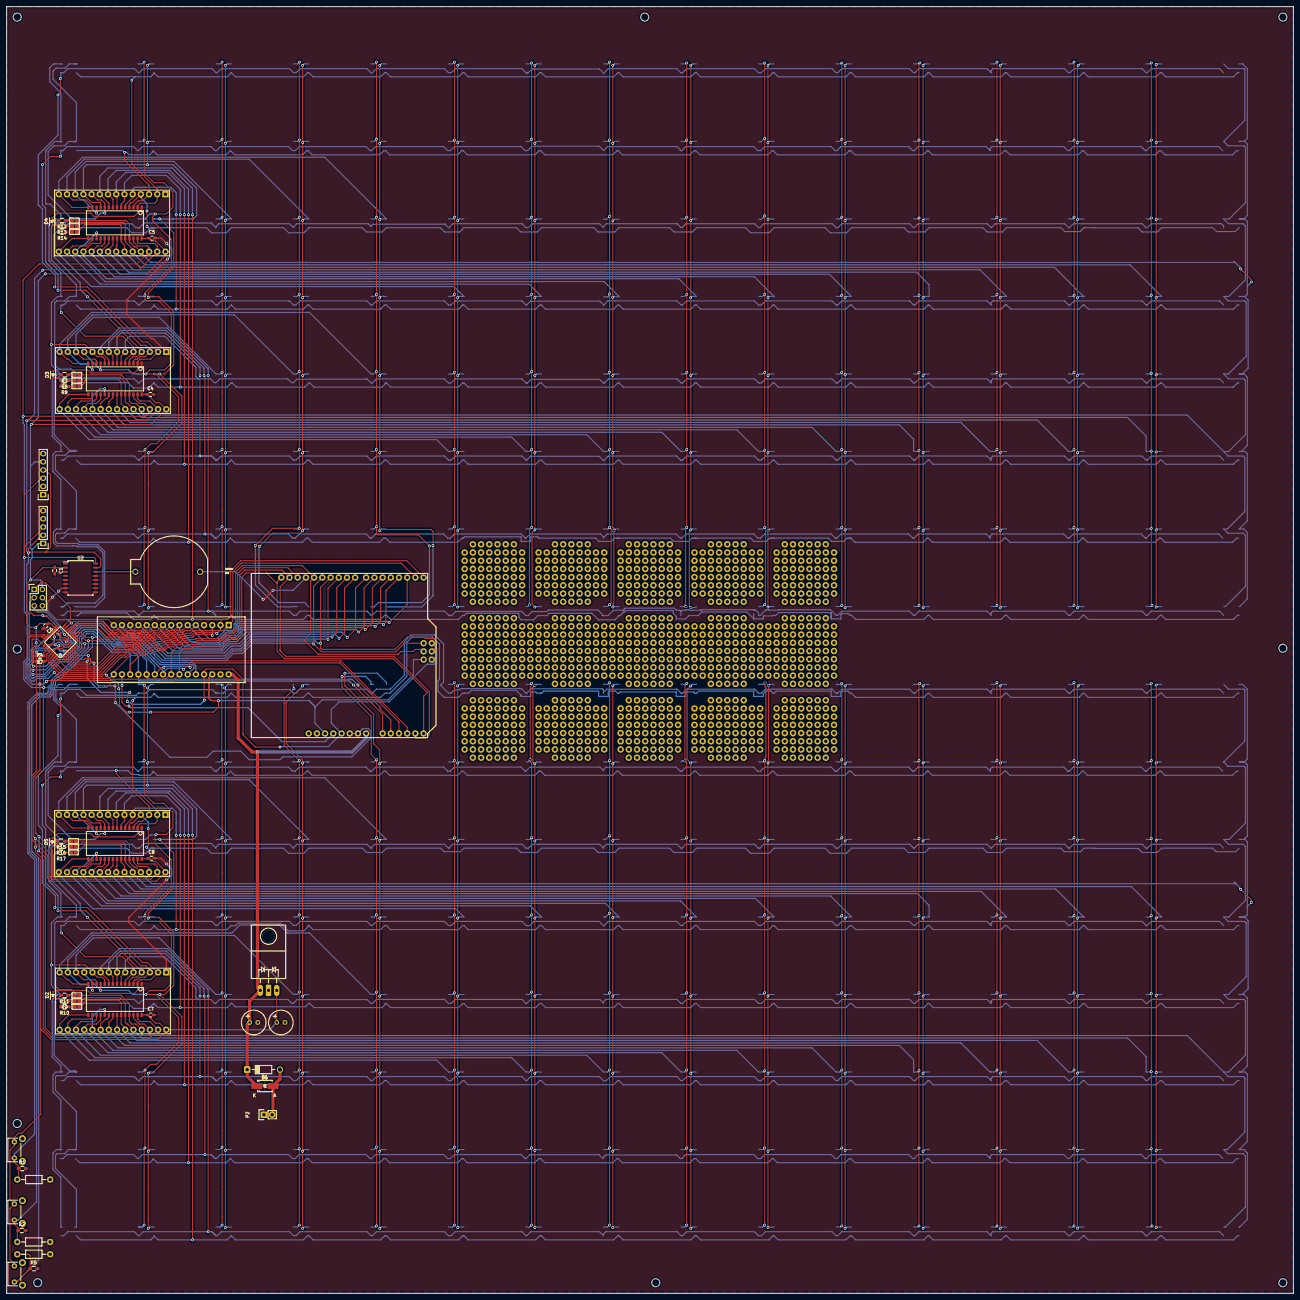
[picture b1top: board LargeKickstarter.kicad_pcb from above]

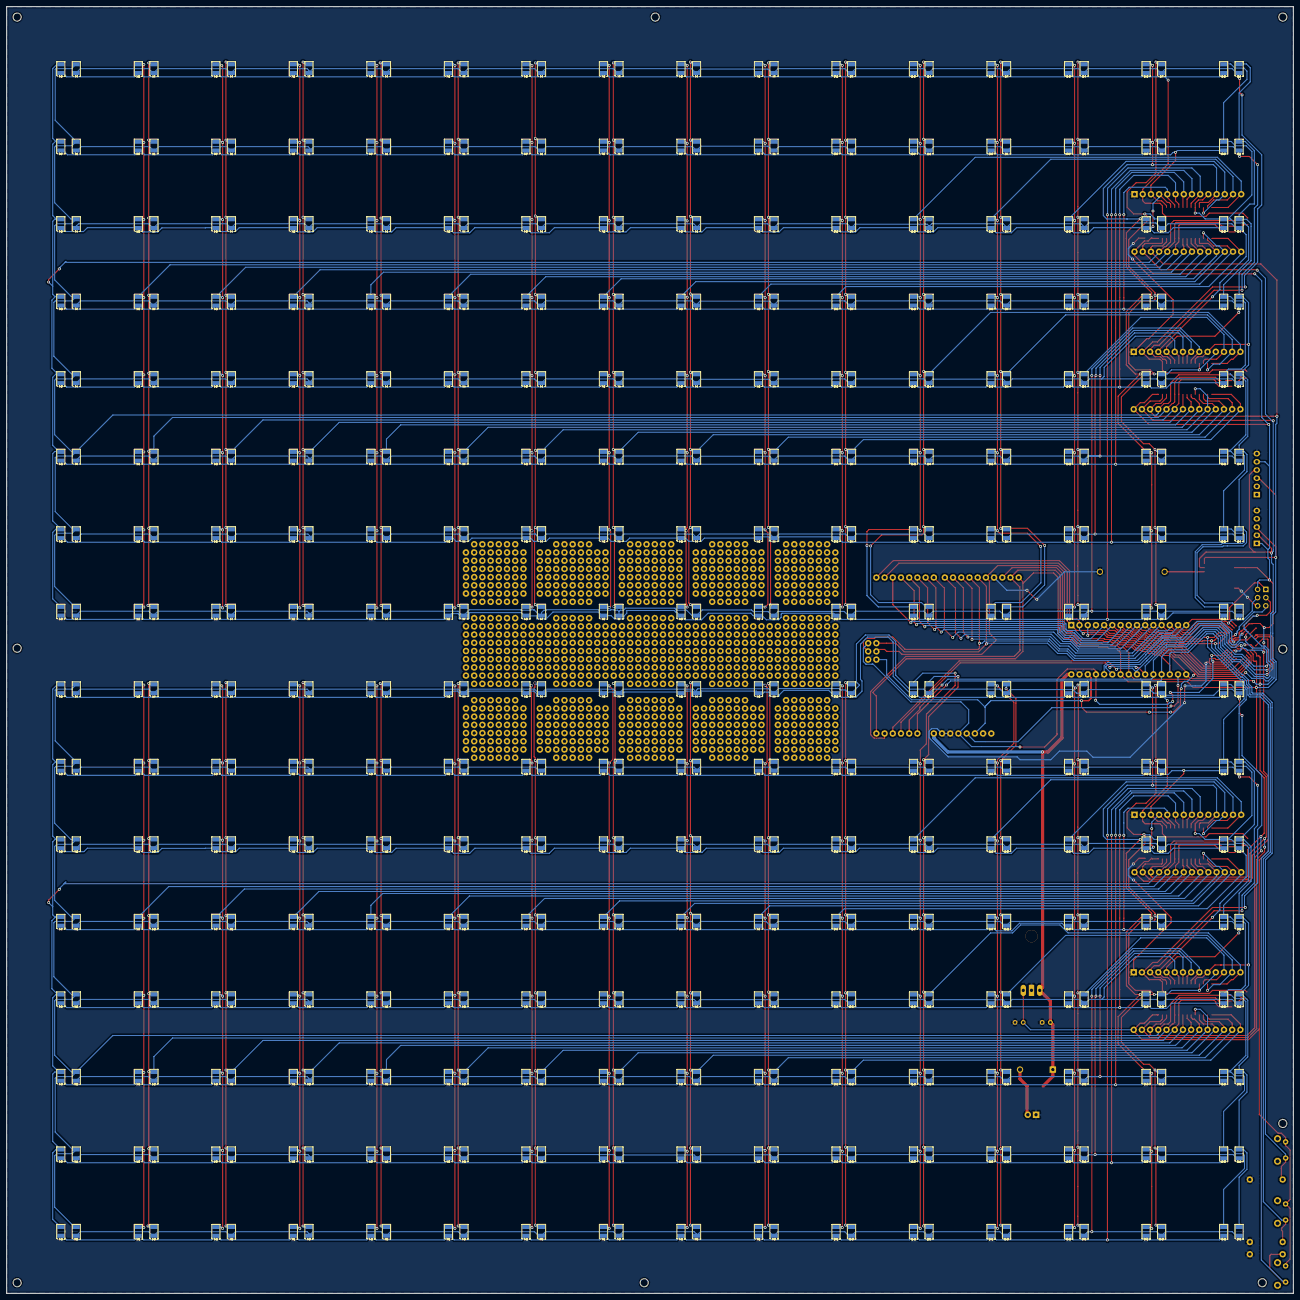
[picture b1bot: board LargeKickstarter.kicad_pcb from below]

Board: 2 copper layers, 398.2 x 398.2 mm, 588 parts (512 on the bottom side), 142 nets.

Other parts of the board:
D6: DIODE; Diode_DO-41_SOD81_Horizontal_RM10
H1, H4, H5, H6, H7, H9, H10: MountingHole_2-5mm
M2, M3: MountingHole_2-5mm
P3: CONN_01X05; Pin_Header_Straight_1x05
P5: CONN_01X06; Pin_Header_Straight_1x06
R18, R19, R20: 10K; Resistor_Horizontal_RM10mm

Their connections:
5: R18.1; also elsewhere on the board
6: R19.1; also elsewhere on the board
7: R20.1; also elsewhere on the board
GND: P3.GND, P5.6, R18.2, R19.2, R20.2; also elsewhere on the board
RAW: D6.2; also elsewhere on the board
SCL: P3.SCL, P5.3; also elsewhere on the board
SDA: P3.SDA, P5.4; also elsewhere on the board
VCC: P3.VCC, P5.5; also elsewhere on the board
Vin: D6.1; also elsewhere on the board

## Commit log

2015-10-09 KiCad Design Files
    Initial add of KiCad Design files
2015-10-09 Inkscape files
    These are the design files for the laser etched faceplates and were
    designed in Inkscape. Quarter time denotes "Quarter til ten in the
    morning", "Half past nine at night". Non-quarter time would be "nine
    forty five in the morning", "nine thirty at night".
2015-10-09 Work In Progress Kickstarter Redesign
    Adding support for plug in modules and through hole components. Adding
    prototyping area.
2015-10-09 Arduino files
    Clock16x16RTC_animations is for non-Quarter time face.
    Clock16x16RTC_q_animations is for quarter time face. matrix_test is
    just all on (good for testing connections after soldering.) Included
    Adafruit libraries and hardware profile for bare Atmega328.
2015-10-09 License Change
    Put my name in it.
2015-10-09 Created README
2015-10-09 Deleted old version.
2015-10-15 Full Redesign
    Doubled LED count. Added footprints for modules. Still need DS3231
    module added.
2015-10-15 Added DS3231 module footprints
2015-10-16 Added Libraries
2015-10-16 Started on silkscreens
2015-10-23 Prelim Gerbers Added
2015-11-06 Further tweaks
    Added PTH components for power section and buttons. Fixed some
    disconnects.
2015-11-07 SVGs
    Generated SVG plot for silkscreen creation
2015-11-07 PCB Tweaks
2015-11-07 Schematic Tweaks
2015-11-09 Finished up new silk screens
2015-11-09 Continuity Check
2015-11-11 Minor tweaks and gerber generation.
2015-11-24 Final changes and publication
